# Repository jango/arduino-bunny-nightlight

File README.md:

# arduino-bunny-nightlight
An Arduino nightlight that looks like a bunny.

# Final Product

# Inspiration
I was inspired by [this blog post] on Sparkfun. However, I wanted to do something more complex in terms of lightning. The bunny shape was laser cut from acrylic and a simple board was assembled to host two RGB LEDs that connected, along with a button to an Arduno Nano board.

There are three modes for this nighlight:

1. solid color (five colors pre-loaded; those can be rotated through by a short button press)
The single button press controls the light mode:
2. pulsating color (same five colors; those can also be rotated through by a short button press)
3. crossfading light (uses the same five colors).

The long button press activates one of the sleep mode durations (turning the light off after 15 / 30 / 60 minutes). A short button press after the sleep mode was activated will cancel it.

# What's Included
1. Eagle schematics for the board<sup name="a1">[1](#f1)</sup>
2. Arduino sketch
 
# What's Not Included
1. The bunny shape vector was not included; you can purchase one from a variery of sites, and it does not even have to be a bunny!

License
----

MIT

Footnotes
----
<b name="f1">1</b> Funny story. I only had a chance to make two iterations of the board and it was my very first time manufacturing a PCB. Being a lengthy and expensive process, I never had the patience to wait for the last iteration of the board to arrive and instead made the LED circuit using a piece of prototyping board. I also used an Arduino Nano instead of a standalone controller that's present in the circuit diagram. Long story short - the circuit included here is about right, but I am not sure if the PCB actually works since it was not untested. [↩](#a1)
[this blog post]:https://learn.sparkfun.com/tutorials/elasto-nightlight

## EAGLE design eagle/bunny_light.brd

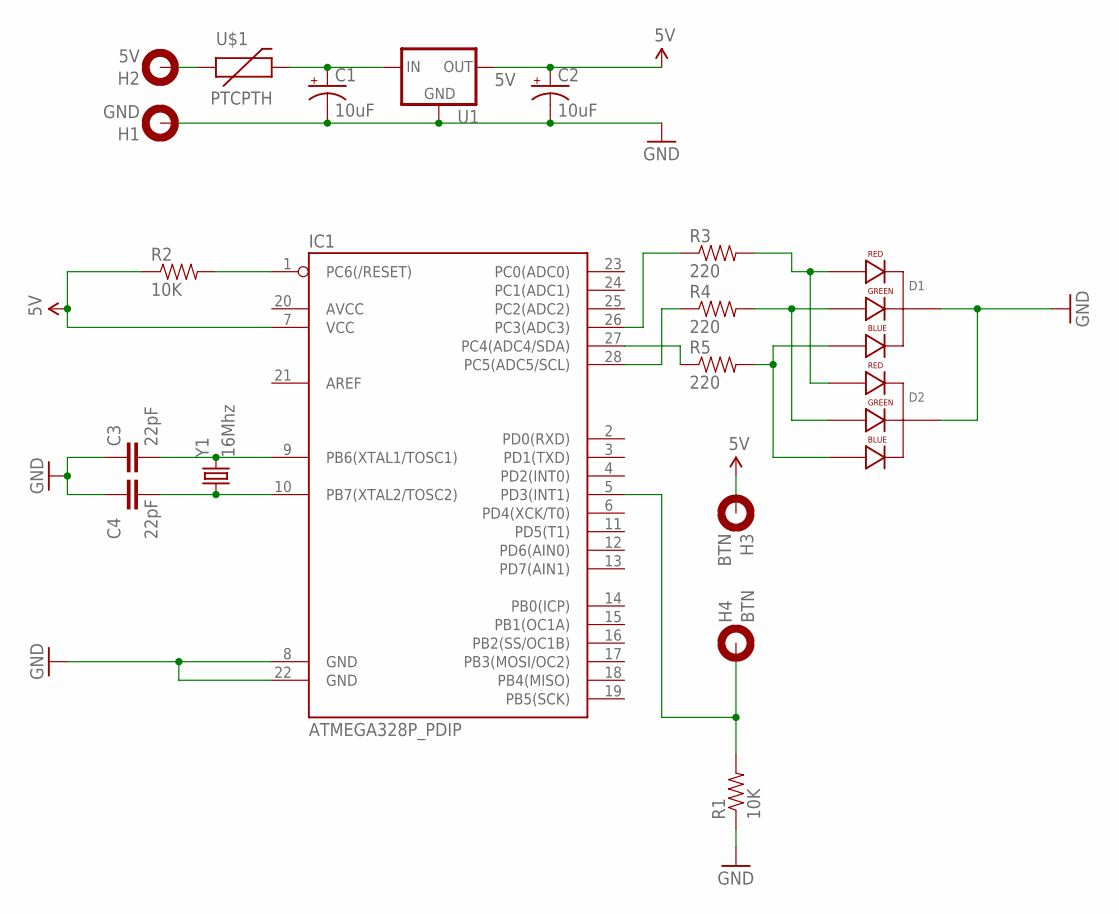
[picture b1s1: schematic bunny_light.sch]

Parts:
C1, C2: 10uF; CPOL-RADIAL-100UF-25V
C3, C4: 22pF; AXIAL-5MM
D1, D2: LED-RGB-CC-THRUCLEAR; LED-RGB-THRU
H1: GND; 2,8-PAD
H2: 5V; 2,8-PAD
H3, H4: BTN; 2,8-PAD
IC1: ATMEGA328P_PDIP; DIL28-3
R1, R2: 10K; AXIAL-0.3EZ
R3, R4, R5: 220; AXIAL-0.3EZ
U1: 5V; 78XXL
U$1: PTCPTH; PTC
Y1: 16Mhz; HC49US

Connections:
5V: C2.1 (+), H3.B2,8, IC1.7 (VCC), R2.P$1 (1), U1.OUT
GND: C1.2 (-), C2.2 (-), C3.P$1 (1), C4.P$1 (1), D1.2 (CATHODE), D2.2 (CATHODE), H1.B2,8, IC1.8 (GND), IC1.22 (GND), R1.P$1 (1), U1.GND
unnamed: C1.1 (+), U1.IN, U$1.P$2 (2)
unnamed: C3.P$2 (2), IC1.9 (PB6(XTAL1/TOSC1)), Y1.2
unnamed: C4.P$2 (2), IC1.10 (PB7(XTAL2/TOSC2)), Y1.1
unnamed: IC1.1 (PC6(/RESET)), R2.P$2 (2)
unnamed: H4.B2,8, IC1.5 (PD3(INT1)), R1.P$2 (2)
unnamed: D1.1 (RED_CATHODE), D2.1 (RED_CATHODE), R3.P$2 (2)
unnamed: D1.3 (GREEN_CATHODE), D2.3 (GREEN_CATHODE), R4.P$2 (2)
unnamed: D1.4 (BLUE_CATHODE), D2.4 (BLUE_CATHODE), R5.P$2 (2)
unnamed: IC1.26 (PC3(ADC3)), R3.P$1 (1)
unnamed: IC1.28 (PC5(ADC5/SCL)), R4.P$1 (1)
unnamed: IC1.27 (PC4(ADC4/SDA)), R5.P$1 (1)
unnamed: H2.B2,8, U$1.P$1 (1)

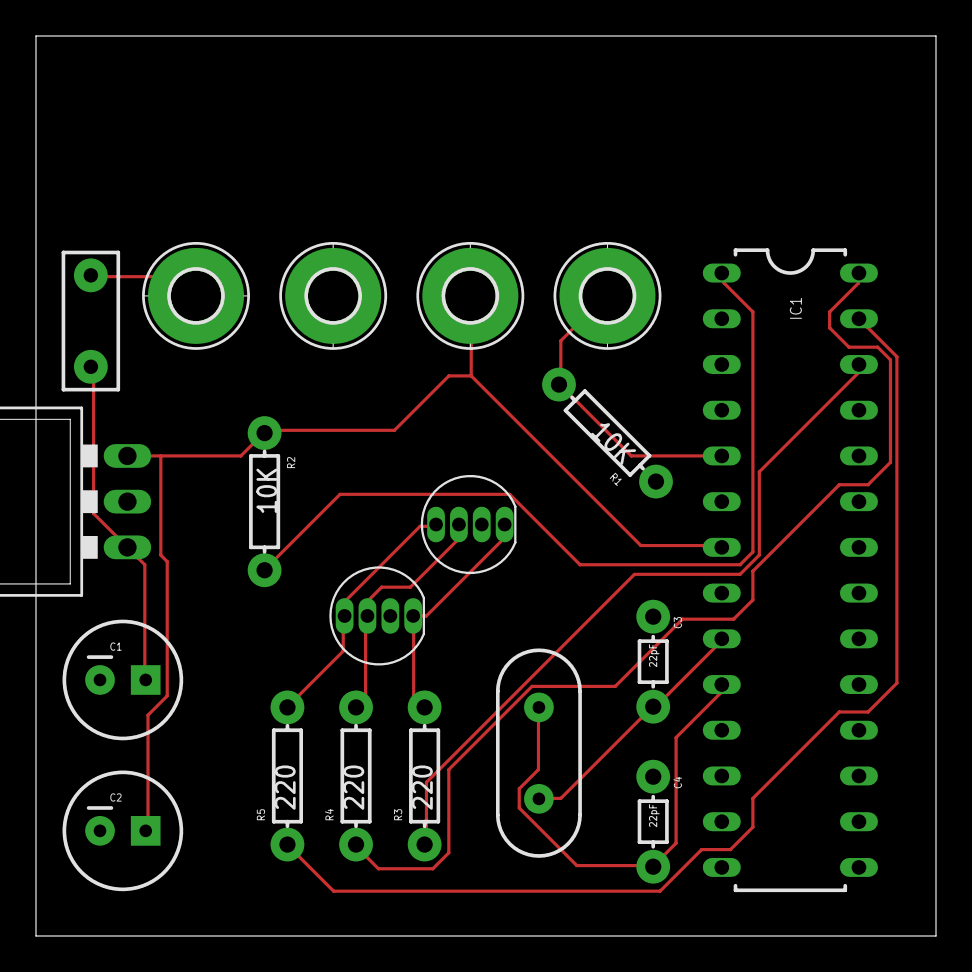
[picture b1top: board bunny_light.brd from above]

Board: 2 copper layers, 50.0 x 50.0 mm, 19 parts (0 on the bottom side), 14 nets.

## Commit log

2016-05-25 - initial commit of the README - initial commit of Eagle design files - initial commit of the sketch
2016-06-11 Second iteration after receiving the board: - corrected wrong components (surface mount vs. through hole) - added PTC fuse - used larger footprints for the resistors - corrected RGB LEDs overlapping
2016-09-08 Updating README.
2016-09-08 Fixing a few typos in the README.
2016-09-08 Fixing README.

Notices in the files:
parts and their libraries:
SparkFun-Capacitors: Licensing: Creative Commons ShareAlike 4.0 International - https://creativecommons.org/licenses/by-sa/4.0
